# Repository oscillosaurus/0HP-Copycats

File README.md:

# 0HP-Copycats
0HP Eurorack Modular passive utilities inspired by the Waveform Magazine Catwalk.

Passive Multiple

Passive Attenuator

Passive Switch

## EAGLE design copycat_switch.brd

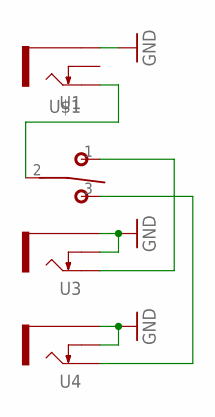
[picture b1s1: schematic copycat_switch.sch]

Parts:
U1, U3, U4: THONKICONNNEW; WQP-PJ301M-12_JACK
U$1: T-80-T-SPDT-ON-OFF-ON; M9040P

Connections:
GND: U1.P$3_SLEEVE (SLEEVE), U3.P$2_SWITCH (SWITCH), U3.P$3_SLEEVE (SLEEVE), U4.P$2_SWITCH (SWITCH), U4.P$3_SLEEVE (SLEEVE)
unnamed: U1.P$1_TIP (TIP), U$1.2
unnamed: U4.P$1_TIP (TIP), U$1.3 (S)
unnamed: U3.P$1_TIP (TIP), U$1.1 (O)

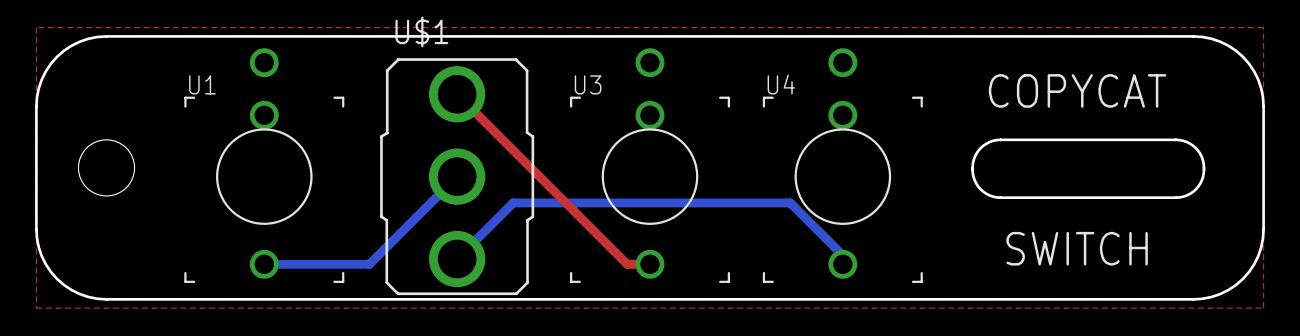
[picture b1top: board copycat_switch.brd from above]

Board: 2 copper layers, 70.0 x 15.0 mm, 4 parts (0 on the bottom side), 4 nets.

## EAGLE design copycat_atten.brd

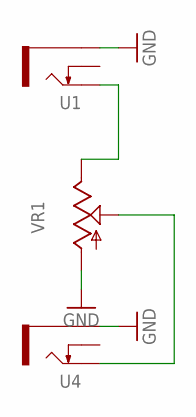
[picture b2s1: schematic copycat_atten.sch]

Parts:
U1, U4: THONKICONNNEW; WQP-PJ301M-12_JACK
VR1: 9MM_SNAP-IN_POT_; 9MM_SNAP-IN_POT

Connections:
GND: U1.P$3_SLEEVE (SLEEVE), U4.P$3_SLEEVE (SLEEVE), VR1.1 (A)
unnamed: U4.P$1_TIP (TIP), VR1.2 (S)
unnamed: U1.P$1_TIP (TIP), VR1.3 (E)

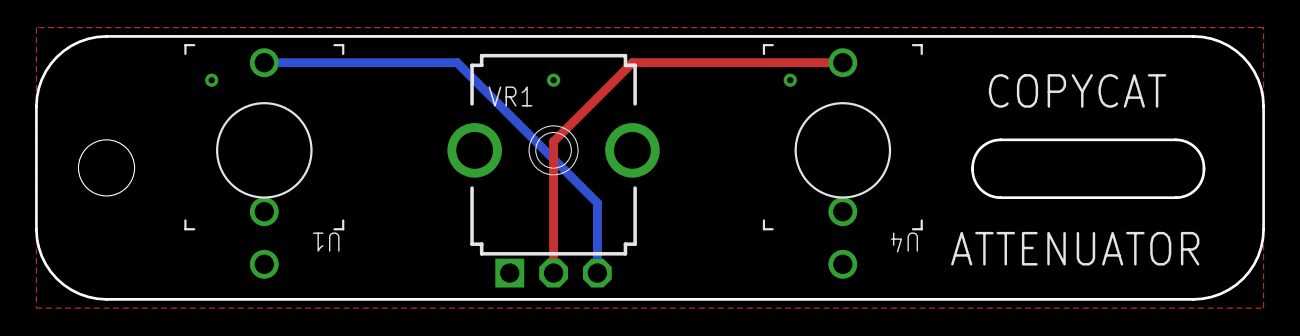
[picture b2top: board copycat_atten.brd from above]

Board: 2 copper layers, 70.0 x 15.0 mm, 3 parts (0 on the bottom side), 3 nets.

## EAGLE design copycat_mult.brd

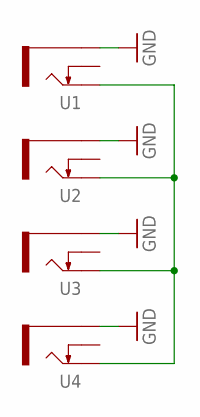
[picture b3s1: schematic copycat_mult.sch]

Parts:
U1, U2, U3, U4: THONKICONNNEW; WQP-PJ301M-12_JACK

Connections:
GND: U1.P$3_SLEEVE (SLEEVE), U2.P$3_SLEEVE (SLEEVE), U3.P$3_SLEEVE (SLEEVE), U4.P$3_SLEEVE (SLEEVE)
unnamed: U1.P$1_TIP (TIP), U2.P$1_TIP (TIP), U3.P$1_TIP (TIP), U4.P$1_TIP (TIP)

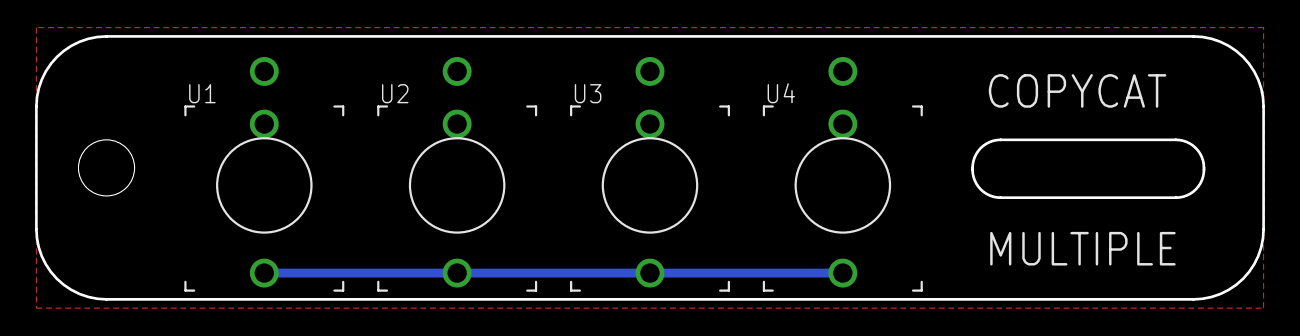
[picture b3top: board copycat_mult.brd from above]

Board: 2 copper layers, 70.0 x 15.0 mm, 4 parts (0 on the bottom side), 2 nets.
